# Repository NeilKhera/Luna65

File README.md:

## Luna65
Luna65 is my first PCB project - a 65% keyboard!

### Disclaimer
This is very much a WIP project which means there will be issues and incomplete features - especially on the software side. This is my first hardware project
and I do not claim to be an expert in the field. While physical versions of the PCB have been tested and are known to work, I do not promise that my implementation
is perfect. For example, the Atmega32u4 microprocessor used in this project does not have sufficient GPIO to enable a clean 5 row x 15 column matrix standard for 65%
keyboards. As such the keys are laid out in an unconventional (and definitely ugly) 6x12 matrix. I do not intend to improve or fix this.

TL;DR This project is provided as is. You are free to use it however you like but I have no intention to polish it into a complete ready-to-ship product. Functionality
may be added or removed at any moment and the project will be abandoned whenever I get too bored to carry on.
(Do, let me know if you actually get some boards made - that'd be sickkkkk!)

### License
Designed by Neil Khera.

Creative Commons Attribution/Share-Alike. See license.txt for additional details.

__

_fin._

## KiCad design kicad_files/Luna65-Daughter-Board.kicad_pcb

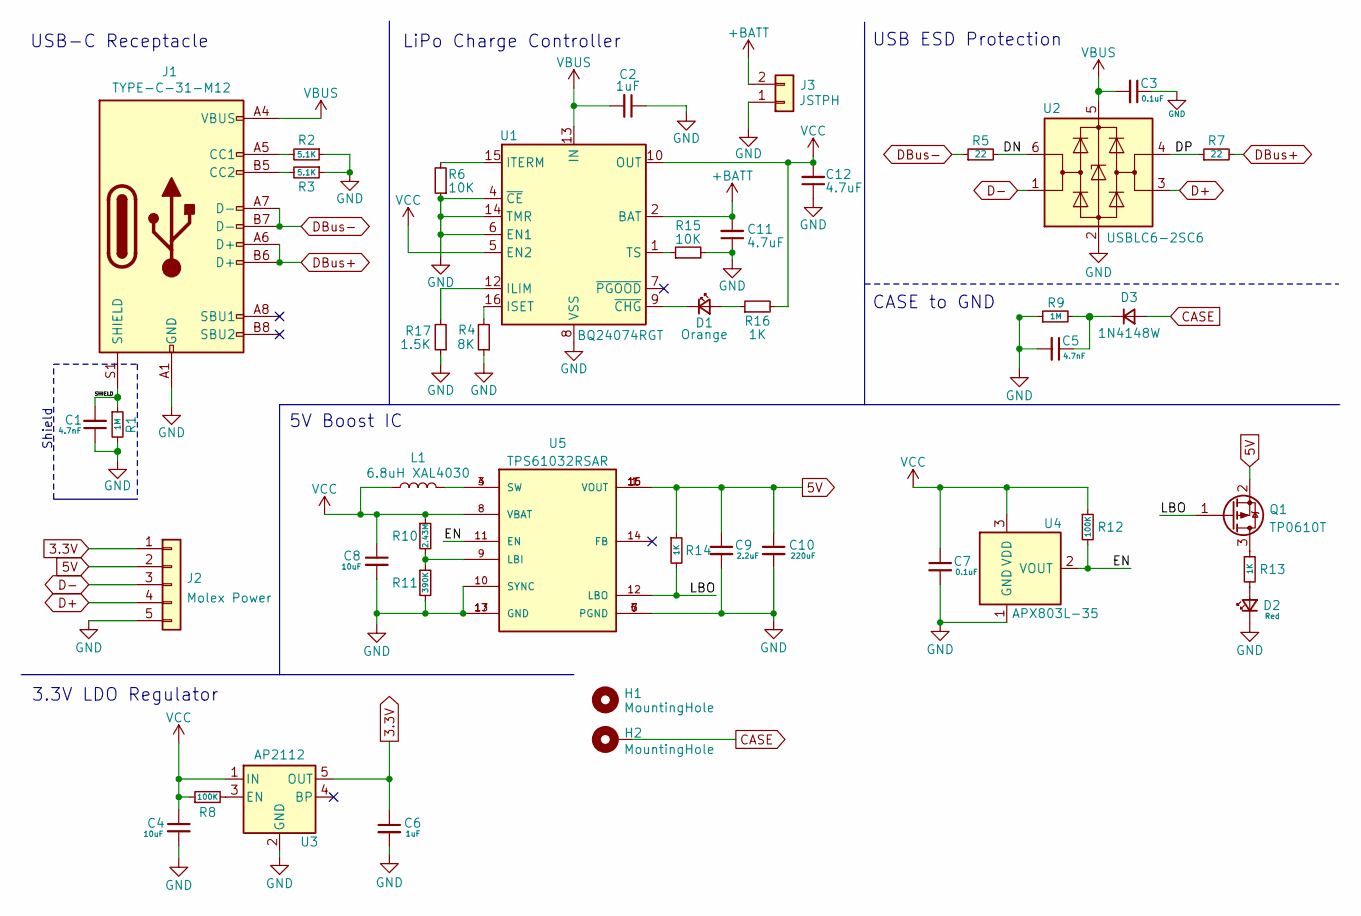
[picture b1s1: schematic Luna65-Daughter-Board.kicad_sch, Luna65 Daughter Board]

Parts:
C1, C5: 4.7nF; C_0603_1608Metric
C2, C6: 1uF; C_0603_1608Metric
C3, C7: 0.1uF; C_0603_1608Metric
C4, C8: 10uF; C_0603_1608Metric
C9: 2.2uF; C_0603_1608Metric
C10: 220uF; C_1206_3216Metric
C11, C12: 4.7uF; C_0603_1608Metric
D1: Orange; LED_0805_2012Metric
D2: Red; LED_0805_2012Metric
D3: 1N4148W; D_SOD-123
H1: MountingHole; MountingHole_2.2mm_M2
H2: MountingHole; MountingHole_2.2mm_M2_Pad
J1: TYPE-C-31-M12; USB_C_Receptacle_Hroparts_TYPE-C-31-M-12
J2: Molex Power; MOLEX_78171-0005
J3: JSTPH; JSTPH2
L1: 6.8uH XAL4030; XAL4030
Q1: TP0610T; SOT-23
R1, R9: 1M; R_0603_1608Metric
R2, R3: 5.1K; R_0603_1608Metric
R4: 8K; R_0603_1608Metric
R5, R7: 22; R_0603_1608Metric
R6, R15: 10K; R_0603_1608Metric
R8, R12: 100K; R_0603_1608Metric
R10: 2.43M; R_0603_1608Metric
R11: 390K; R_0603_1608Metric
R13, R14, R16: 1K; R_0603_1608Metric
R17: 1.5K; R_0603_1608Metric
U1: BQ24074RGT; VQFN-16-1EP_3x3mm_P0.5mm_EP1.6x1.6mm
U2: USBLC6-2SC6; SOT-23-6
U3: AP2112; SOT-23-5
U4: APX803L-35; SOT-23
U5: TPS61032RSAR; Texas_S-PVQFN-N16_EP2.7x2.7mm

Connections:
3.3V: C6.1, J2.1, U3.5 (OUT)
5V: C9.1, C10.1, J2.2, Q1.2 (S), R14.1, U5.1 (VOUT), U5.15 (VOUT), U5.16 (VOUT)
+BATT: C11.2, J3.2, U1.2 (BAT), U1.3 (BAT)
/DN: R5.2, U2.6 (I/O1)
/DP: R7.1, U2.4 (I/O2)
/EN: R12.2, U4.2 (VOUT), U5.11 (EN)
/LBO: Q1.1 (G), R14.2, U5.12 (LBO)
/SHIELD: C1.2, J1.S1 (SHIELD), R1.1
CASE: D3.2 (A), H2.1
D+: J2.4, U2.3 (I/O2)
D-: J2.3, U2.1 (I/O1)
DBus+: J1.A6 (D+), J1.B6 (D+), R7.2
DBus-: J1.A7 (D-), J1.B7 (D-), R5.1
GND: C1.1, C2.1, C3.1, C4.2, C5.2, C6.2, C7.2, C8.2, C9.2, C10.2, C11.1, C12.1, D2.1 (K), J1.A1 (GND), J1.B1 (GND), J2.5, J3.1, R1.2, R2.1, R3.1, R4.1, R6.1, R9.1, R11.2, R15.2, R17.1, U1.4 (~CE), U1.6 (EN1), U1.8 (VSS), U1.14 (TMR), U1.17 (VSS), U2.2 (GND), U3.2 (GND), U4.1 (GND), U5.5 (PGND), U5.6 (PGND), U5.7 (PGND), U5.10 (SYNC), U5.13 (GND), U5.17 (GND)
unnamed: C5.1, D3.1 (K), R9.2
unnamed: D1.1 (K), U1.9 (~CHG)
unnamed: D1.2 (A), R16.1
unnamed: D2.2 (A), R13.2
unnamed: J1.A5 (CC1), R2.2
unnamed: J1.B5 (CC2), R3.2
unnamed: L1.2, U5.3 (SW), U5.4 (SW)
unnamed: Q1.3 (D), R13.1
unnamed: R4.2, U1.16 (ISET)
unnamed: R6.2, U1.15 (ITERM)
unnamed: R8.2, U3.3 (EN)
unnamed: R10.2, R11.1, U5.9 (LBI)
unnamed: R15.1, U1.1 (TS)
unnamed: R17.2, U1.12 (ILIM)
VBUS: C2.2, C3.2, J1.A4 (VBUS), J1.B4 (VBUS), U1.13 (IN), U2.5 (VBUS)
VCC: C4.1, C7.1, C8.1, C12.2, L1.1, R8.1, R10.1, R12.1, R16.2, U1.5 (EN2), U1.10 (OUT), U1.11 (OUT), U3.1 (IN), U4.3 (VDD), U5.8 (VBAT)

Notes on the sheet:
3.3V LDO Regulator
5V Boost IC
CASE to GND
USB-C Receptacle
LiPo Charge Controller
Shield
USB ESD Protection

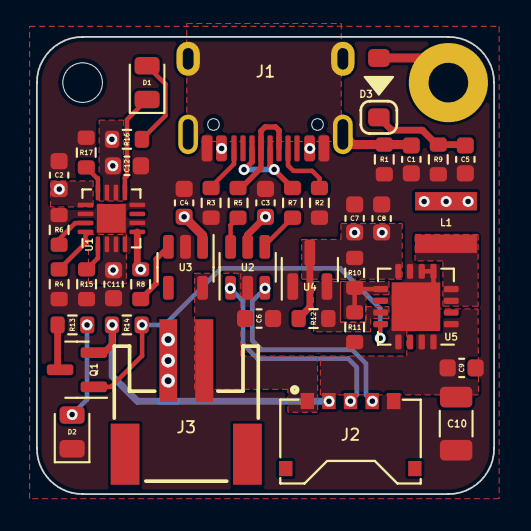
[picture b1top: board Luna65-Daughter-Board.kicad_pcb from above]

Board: 2 copper layers, 25.4 x 25.4 mm, 44 parts (0 on the bottom side), 30 nets.

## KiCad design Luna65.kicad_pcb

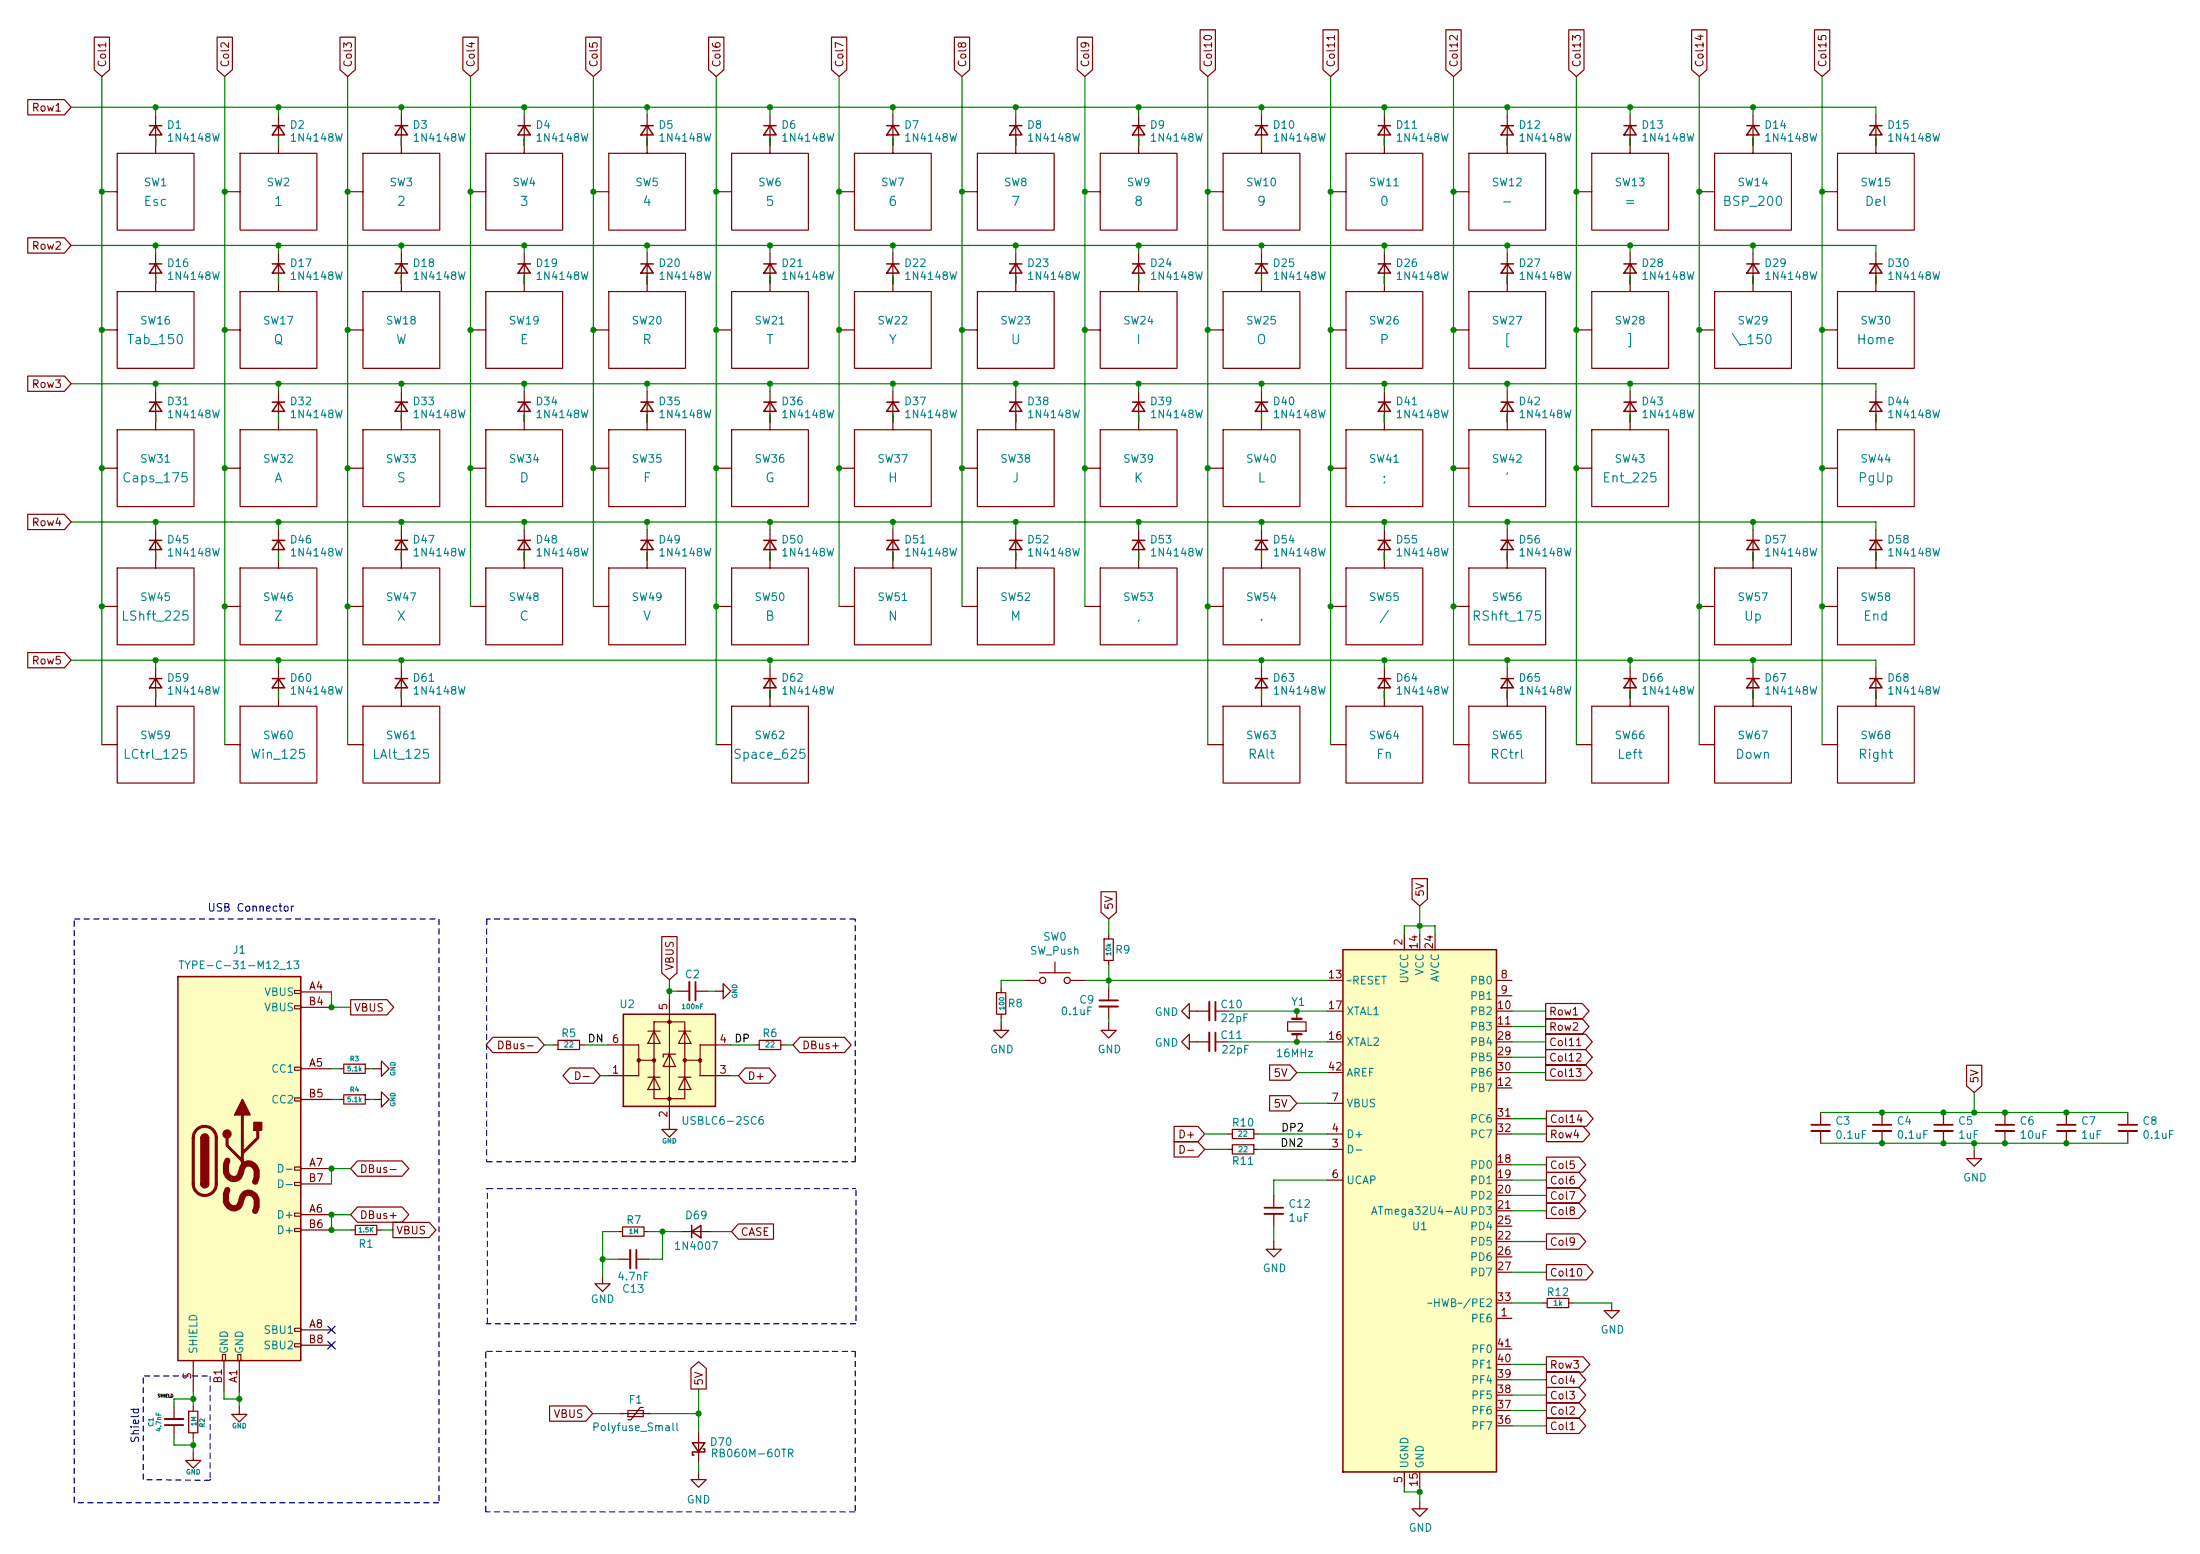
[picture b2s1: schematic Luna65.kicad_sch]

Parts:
C1, C13: 4.7nF; C_0805_2012Metric
C2: 100nF; C_0805_2012Metric
C3, C4, C8, C9: 0.1uF; C_0805_2012Metric
C5, C7, C12: 1uF; C_0805_2012Metric
C6: 10uF; C_0805_2012Metric
C10, C11: 22pF; C_0805_2012Metric
D1, D2, D3, D4, D5, D6, D7, D8, D9, D10, D11, D12, D13, D14, D15, D16, D17, D18, D19, D20, D21, D22, D23, D24, D25, D26, D27, D28, D29, D30, D31, D32, D33, D34, D35, D36, D37, D38, D39, D40, D41, D42, D43, D44, D45, D46, D47, D48, D49, D50, D51, D52, D53, D54, D55, D56, D57, D58, D59, D60, D61, D62, D63, D64, D65, D66, D67, D68: 1N4148W; D_SOD-123
D69: 1N4007; D_SOD-123
D70: RB060M-60TR; D_SOD-123
F1: Polyfuse_Small; Fuse_1812_4532
J1: TYPE-C-31-M12_13; TYPE-C-31-M-12
R1: 1.5K; R_SMD_1206
R2, R7: 1M; R_SMD_1206
R3, R4: 5.1k; R_SMD_1206
R5, R6, R10, R11: 22; R_SMD_1206
R8: 100; R_SMD_1206
R9: 10k; R_SMD_1206
R12: 1k; R_SMD_1206
SW0: SW_Push; SW_Push_1P1T_NO_CK_KMR2
SW1: Esc; MX100H
SW2: 1; MX100H
SW3: 2; MX100H
SW4: 3; MX100H
SW5: 4; MX100H
SW6: 5; MX100H
SW7: 6; MX100H
SW8: 7; MX100H
SW9: 8; MX100H
SW10: 9; MX100H
SW11: 0; MX100H
SW12: -; MX100H
SW13: =; MX100H
SW14: BSP_200; MX200H
SW15: Del; MX100H
SW16: Tab_150; MX150H
SW17: Q; MX100H
SW18: W; MX100H
SW19: E; MX100H
SW20: R; MX100H
SW21: T; MX100H
SW22: Y; MX100H
SW23: U; MX100H
SW24: I; MX100H
SW25: O; MX100H
SW26: P; MX100H
SW27: [; MX100H
SW28: ]; MX100H
SW29: \_150; MX150H
SW30: Home; MX100H
SW31: Caps_175; MX175H
SW32: A; MX100H
SW33: S; MX100H
SW34: D; MX100H
SW35: F; MX100H
SW36: G; MX100H
SW37: H; MX100H
SW38: J; MX100H
SW39: K; MX100H
SW40: L; MX100H
SW41: ;; MX100H
SW42: '; MX100H
SW43: Ent_225; MX225H
SW44: PgUp; MX100H
SW45: LShft_225; MX225H
SW46: Z; MX100H
SW47: X; MX100H
SW48: C; MX100H
SW49: V; MX100H
SW50: B; MX100H
SW51: N; MX100H
SW52: M; MX100H
SW53: ,; MX100H
SW54: .; MX100H
SW55: /; MX100H
SW56: RShft_175; MX175H
SW57: Up; MX100H
SW58: End; MX100H
SW59: LCtrl_125; MX125H
SW60: Win_125; MX125H
SW61: LAlt_125; MX125H
SW62: Space_625; MX625H
SW63: RAlt; MX100H
SW64: Fn; MX100H
SW65: RCtrl; MX100H
SW66: Left; MX100H
SW67: Down; MX100H
SW68: Right; MX100H
U1: ATmega32U4-AU; TQFP-44_10x10mm_P0.8mm
U2: USBLC6-2SC6; SOT-23-6
Y1: 16MHz; Crystal_SMD_5032-2Pin_5.0x3.2mm_HandSoldering

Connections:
5V: C3.1, C4.1, C5.1, C6.1, C7.1, C8.1, D70.2 (A), F1.2, R9.1, U1.2 (UVCC), U1.7 (VBUS), U1.14 (VCC), U1.24 (AVCC), U1.34 (VCC), U1.42 (AREF), U1.44 (AVCC)
/DN: R5.2, U2.6 (I/O1)
/DN2: R11.1, U1.3 (D-)
/DP: R6.1, U2.4 (I/O2)
/DP2: R10.1, U1.4 (D+)
/SHIELD: C1.2, J1.S (SHIELD), R2.1
CASE: D69.2 (A)
Col1: SW1.1 (Col), SW16.1 (Col), SW31.1 (Col), SW45.1 (Col), SW59.1 (Col), U1.36 (PF7)
Col2: SW2.1 (Col), SW17.1 (Col), SW32.1 (Col), SW46.1 (Col), SW60.1 (Col), U1.37 (PF6)
Col3: SW3.1 (Col), SW18.1 (Col), SW33.1 (Col), SW47.1 (Col), SW61.1 (Col), U1.38 (PF5)
Col4: SW4.1 (Col), SW19.1 (Col), SW34.1 (Col), SW48.1 (Col), U1.39 (PF4)
Col5: SW5.1 (Col), SW20.1 (Col), SW35.1 (Col), SW49.1 (Col), U1.18 (PD0)
Col6: SW6.1 (Col), SW21.1 (Col), SW36.1 (Col), SW50.1 (Col), SW62.1 (Col), U1.19 (PD1)
Col7: SW7.1 (Col), SW22.1 (Col), SW37.1 (Col), SW51.1 (Col), U1.20 (PD2)
Col8: SW8.1 (Col), SW23.1 (Col), SW38.1 (Col), SW52.1 (Col), U1.21 (PD3)
Col9: SW9.1 (Col), SW24.1 (Col), SW39.1 (Col), SW53.1 (Col), U1.22 (PD5)
Col10: SW10.1 (Col), SW25.1 (Col), SW40.1 (Col), SW54.1 (Col), SW63.1 (Col), U1.27 (PD7)
Col11: SW11.1 (Col), SW26.1 (Col), SW41.1 (Col), SW55.1 (Col), SW64.1 (Col), U1.28 (PB4)
Col12: SW12.1 (Col), SW27.1 (Col), SW42.1 (Col), SW56.1 (Col), SW65.1 (Col), U1.29 (PB5)
Col13: SW13.1 (Col), SW28.1 (Col), SW43.1 (Col), SW66.1 (Col), U1.30 (PB6)
Col14: SW14.1 (Col), SW29.1 (Col), SW57.1 (Col), SW67.1 (Col), U1.31 (PC6)
Col15: SW15.1 (Col), SW30.1 (Col), SW44.1 (Col), SW58.1 (Col), SW68.1 (Col)
D+: R10.2, U2.3 (I/O2)
D-: R11.2, U2.1 (I/O1)
DBus+: J1.A6 (D+), J1.B6 (D+), R1.1, R6.2
DBus-: J1.A7 (D-), J1.B7 (D-), R5.1
GND: C1.1, C2.1, C3.2, C4.2, C5.2, C6.2, C7.2, C8.2, C9.2, C10.2, C11.2, C12.2, C13.2, D70.1 (K), J1.A1 (GND), J1.B1 (GND), R2.2, R3.1, R4.1, R7.1, R8.2, R12.1, U1.5 (UGND), U1.15 (GND), U1.23 (GND), U1.35 (GND), U1.43 (GND), U2.2 (GND)
unnamed: C9.1, R9.2, SW0.2, U1.13 (~RESET)
unnamed: C10.1, U1.17 (XTAL1), Y1.2
unnamed: C11.1, U1.16 (XTAL2), Y1.1
unnamed: C12.1, U1.6 (UCAP)
unnamed: C13.1, D69.1 (K), R7.2
unnamed: D1.2 (A), SW1.2 (Row)
unnamed: D2.2 (A), SW2.2 (Row)
unnamed: D3.2 (A), SW3.2 (Row)
unnamed: D4.2 (A), SW4.2 (Row)
unnamed: D5.2 (A), SW5.2 (Row)
unnamed: D6.2 (A), SW6.2 (Row)
unnamed: D7.2 (A), SW7.2 (Row)
unnamed: D8.2 (A), SW8.2 (Row)
unnamed: D9.2 (A), SW9.2 (Row)
unnamed: D10.2 (A), SW10.2 (Row)
unnamed: D11.2 (A), SW11.2 (Row)
unnamed: D12.2 (A), SW12.2 (Row)
unnamed: D13.2 (A), SW13.2 (Row)
unnamed: D14.2 (A), SW14.2 (Row)
unnamed: D15.2 (A), SW15.2 (Row)
unnamed: D16.2 (A), SW16.2 (Row)
unnamed: D17.2 (A), SW17.2 (Row)
unnamed: D18.2 (A), SW18.2 (Row)
unnamed: D19.2 (A), SW19.2 (Row)
unnamed: D20.2 (A), SW20.2 (Row)
unnamed: D21.2 (A), SW21.2 (Row)
unnamed: D22.2 (A), SW22.2 (Row)
unnamed: D23.2 (A), SW23.2 (Row)
unnamed: D24.2 (A), SW24.2 (Row)
unnamed: D25.2 (A), SW25.2 (Row)
unnamed: D26.2 (A), SW26.2 (Row)
unnamed: D27.2 (A), SW27.2 (Row)
unnamed: D28.2 (A), SW28.2 (Row)
unnamed: D29.2 (A), SW29.2 (Row)
unnamed: D30.2 (A), SW30.2 (Row)
unnamed: D31.2 (A), SW31.2 (Row)
unnamed: D32.2 (A), SW32.2 (Row)
unnamed: D33.2 (A), SW33.2 (Row)
unnamed: D34.2 (A), SW34.2 (Row)
unnamed: D35.2 (A), SW35.2 (Row)
unnamed: D36.2 (A), SW36.2 (Row)
unnamed: D37.2 (A), SW37.2 (Row)
unnamed: D38.2 (A), SW38.2 (Row)
unnamed: D39.2 (A), SW39.2 (Row)
unnamed: D40.2 (A), SW40.2 (Row)
unnamed: D41.2 (A), SW41.2 (Row)
unnamed: D42.2 (A), SW42.2 (Row)
unnamed: D43.2 (A), SW43.2 (Row)
unnamed: D44.2 (A), SW44.2 (Row)
unnamed: D45.2 (A), SW45.2 (Row)
unnamed: D46.2 (A), SW46.2 (Row)
unnamed: D47.2 (A), SW47.2 (Row)
unnamed: D48.2 (A), SW48.2 (Row)
unnamed: D49.2 (A), SW49.2 (Row)
unnamed: D50.2 (A), SW50.2 (Row)
unnamed: D51.2 (A), SW51.2 (Row)
unnamed: D52.2 (A), SW52.2 (Row)
unnamed: D53.2 (A), SW53.2 (Row)
unnamed: D54.2 (A), SW54.2 (Row)
unnamed: D55.2 (A), SW55.2 (Row)
unnamed: D56.2 (A), SW56.2 (Row)
unnamed: D57.2 (A), SW57.2 (Row)
unnamed: D58.2 (A), SW58.2 (Row)
unnamed: D59.2 (A), SW59.2 (Row)
unnamed: D60.2 (A), SW60.2 (Row)
unnamed: D61.2 (A), SW61.2 (Row)
unnamed: D62.2 (A), SW62.2 (Row)
unnamed: D63.2 (A), SW63.2 (Row)
unnamed: D64.2 (A), SW64.2 (Row)
unnamed: D65.2 (A), SW65.2 (Row)
unnamed: D66.2 (A), SW66.2 (Row)
unnamed: D67.2 (A), SW67.2 (Row)
unnamed: D68.2 (A), SW68.2 (Row)
unnamed: J1.A5 (CC1), R3.2
unnamed: J1.B5 (CC2), R4.2
unnamed: R8.1, SW0.1
unnamed: R12.2, U1.33 (~HWB~/PE2)
Row1: D1.1 (K), D2.1 (K), D3.1 (K), D4.1 (K), D5.1 (K), D6.1 (K), D7.1 (K), D8.1 (K), D9.1 (K), D10.1 (K), D11.1 (K), D12.1 (K), D13.1 (K), D14.1 (K), D15.1 (K), U1.10 (PB2)
Row2: D16.1 (K), D17.1 (K), D18.1 (K), D19.1 (K), D20.1 (K), D21.1 (K), D22.1 (K), D23.1 (K), D24.1 (K), D25.1 (K), D26.1 (K), D27.1 (K), D28.1 (K), D29.1 (K), D30.1 (K), U1.11 (PB3)
Row3: D31.1 (K), D32.1 (K), D33.1 (K), D34.1 (K), D35.1 (K), D36.1 (K), D37.1 (K), D38.1 (K), D39.1 (K), D40.1 (K), D41.1 (K), D42.1 (K), D43.1 (K), D44.1 (K), U1.40 (PF1)
Row4: D45.1 (K), D46.1 (K), D47.1 (K), D48.1 (K), D49.1 (K), D50.1 (K), D51.1 (K), D52.1 (K), D53.1 (K), D54.1 (K), D55.1 (K), D56.1 (K), D57.1 (K), D58.1 (K), U1.32 (PC7)
Row5: D59.1 (K), D60.1 (K), D61.1 (K), D62.1 (K), D63.1 (K), D64.1 (K), D65.1 (K), D66.1 (K), D67.1 (K), D68.1 (K)
VBUS: C2.2, F1.1, J1.A4 (VBUS), J1.B4 (VBUS), R1.2, U2.5 (VBUS)

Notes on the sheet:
Shield
USB Connector

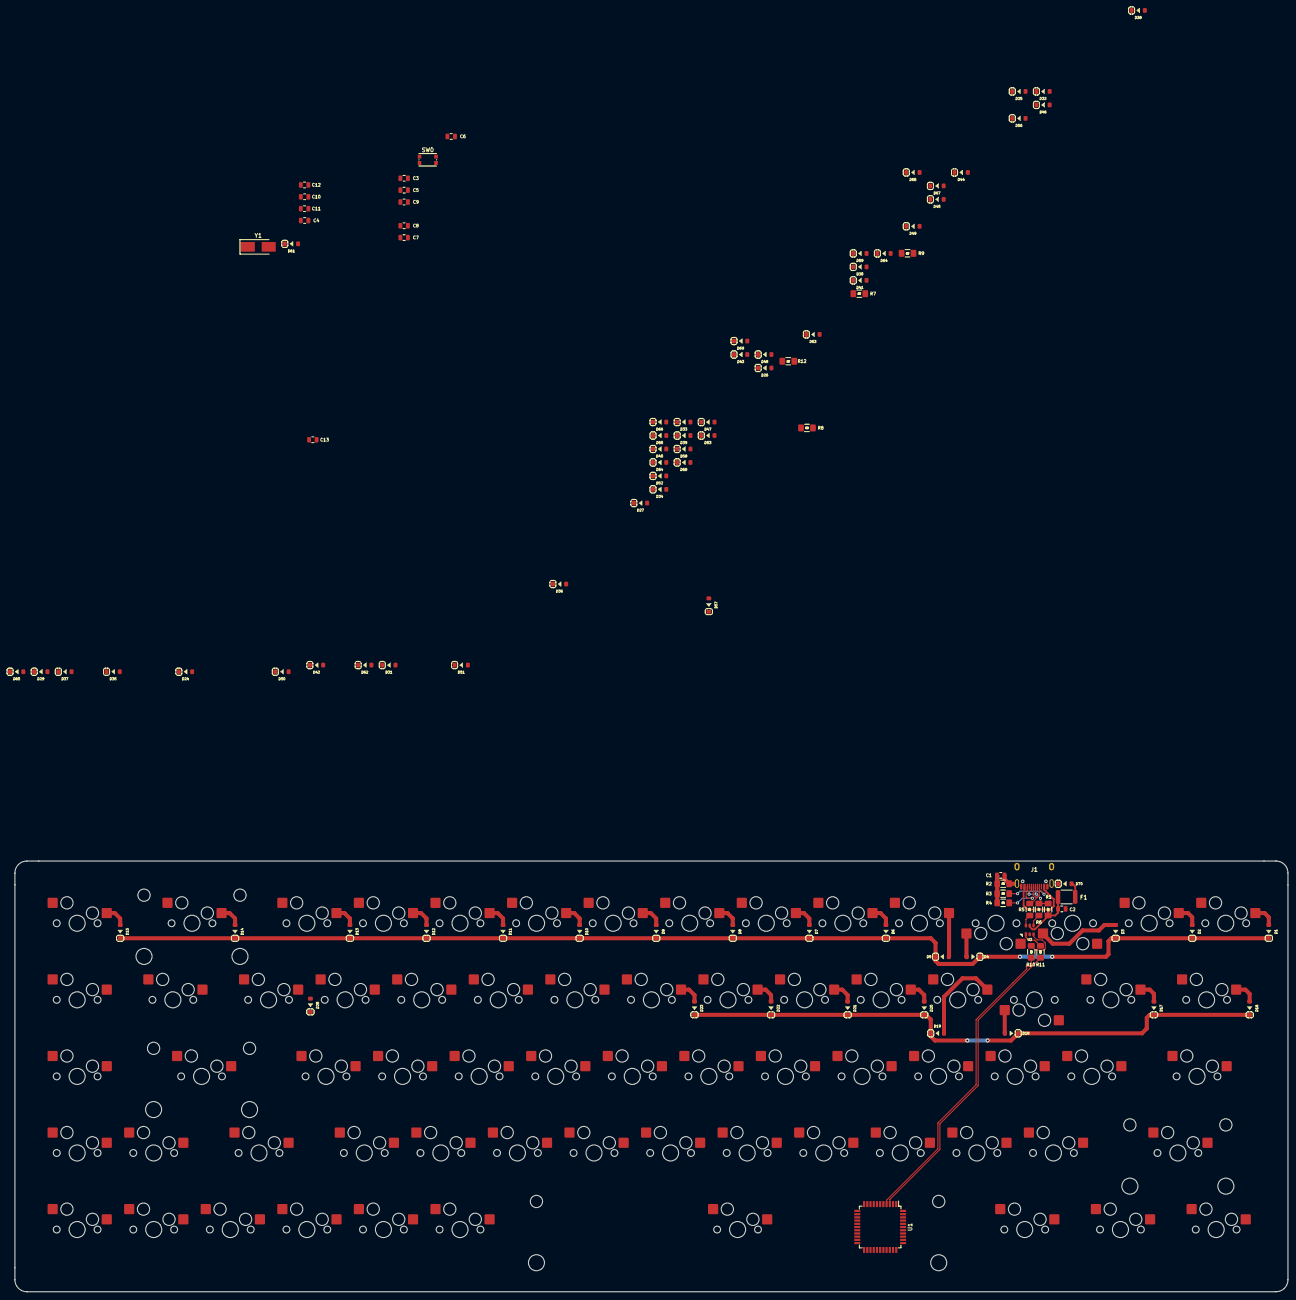
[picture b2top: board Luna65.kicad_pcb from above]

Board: 2 copper layers, 316.7 x 107.2 mm, 169 parts (0 on the bottom side), 109 nets.

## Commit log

2021-08-05 Add Files
2021-08-05 Add Acheron Library as submodule
2021-08-05 Update Paths
2021-08-17 Add QMK Firmware Folder
2021-08-17 Backlink to CADLAB.io has been added.
2021-08-18 Luna65 Changes
2021-08-19 Completed routing
2021-09-03 Add New Firmware
2021-09-09 CAD files
2021-09-12 Schematic fixes. Prep for LEDs
2021-09-12 Folder Cleanup
2021-09-29 V3 Changes
2021-10-05 Done with v3
2021-10-13 firmware updates
2021-10-17 Stuff idk
2021-11-02 Added DXFs
2021-11-05 Update Firmware
2021-11-07 new changes for v4
2021-11-09 Finished V4 routing
2021-11-16 stuff
2021-11-19 Firmware V4
2021-11-27 Rev 5
2021-12-08 Fixed Broken Bluetooth
2021-12-08 Update Schematic Ver
2021-12-09 Better BT keepout zone
2021-12-11 Final (?) Updates
2021-12-12 Updated Case DXF
2022-02-12 Refactoring 1
2022-02-16 Rev 6 initial changes
2022-02-17 Rev 6 pre-production updates
2022-02-26 DB Rev B
2022-03-04 DB Rev C
2022-03-09 Updated QMK firmware to support RGB. Cleaned up routing somewhat
2022-03-09 Added 0 Ohm resistor to isolate BT and uC 3.3V
2022-03-09 Finished Daughterboard 3D model
2022-03-12 Limit RGB max brightness
2022-03-13 Fixed Del keycode location
2022-03-19 Added Gasket Mount Plate DXF
2022-04-01 DB Rev 4 Changes
2022-04-07 Added Gasket mount case design
2022-06-13 V7 Changes
2022-09-13 DB Rev 8
